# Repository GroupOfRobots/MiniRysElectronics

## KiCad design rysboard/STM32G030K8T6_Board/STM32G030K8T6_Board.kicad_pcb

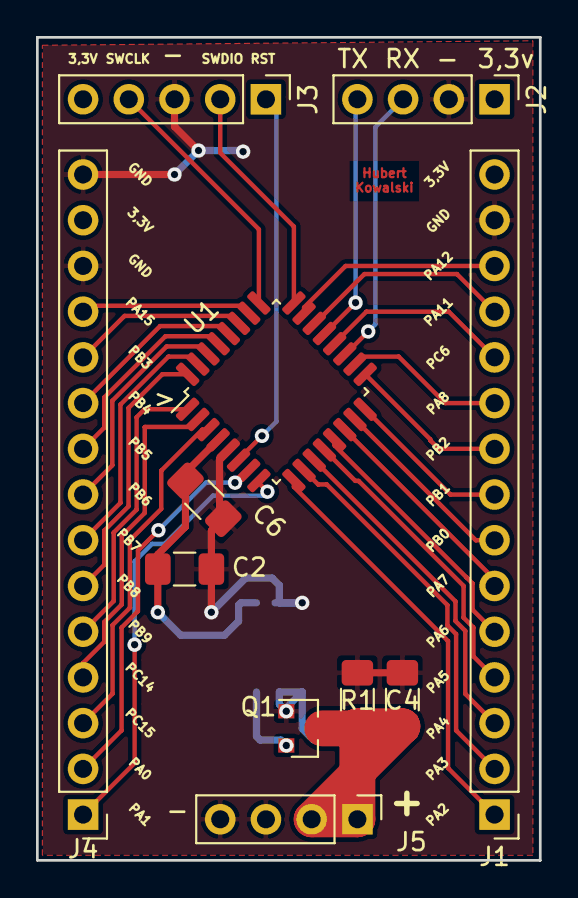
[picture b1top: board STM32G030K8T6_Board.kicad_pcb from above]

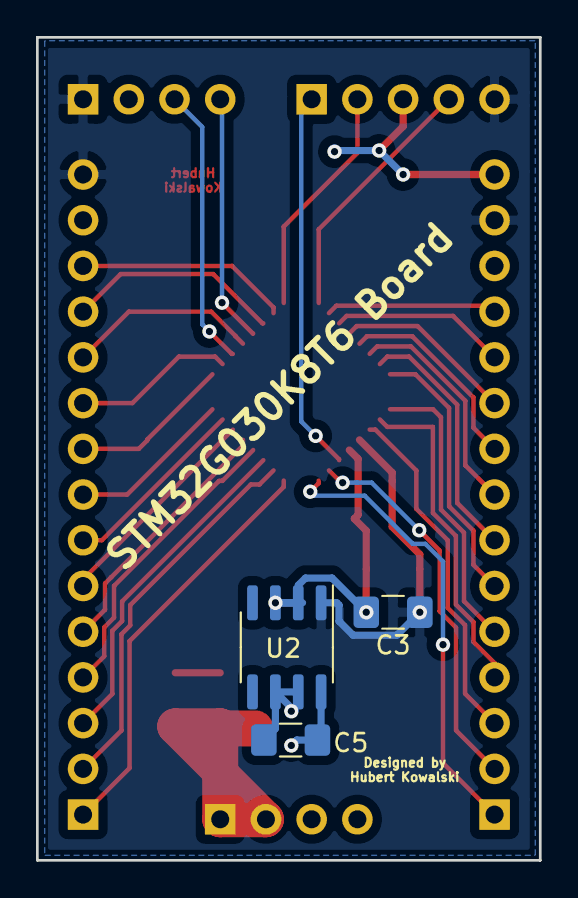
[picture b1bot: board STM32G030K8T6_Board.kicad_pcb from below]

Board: 2 copper layers, 27.9 x 45.7 mm, 14 parts (3 on the bottom side), 34 nets.

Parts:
C2, C5: 1uF; C_1206_3216Metric_Pad1.42x1.75mm_HandSolder
C3, C4, C6: 100nF; C_1206_3216Metric_Pad1.42x1.75mm_HandSolder
J1, J4: Conn_01x15; PinHeader_1x15_P2.54mm_Vertical
J2, J5: Conn_01x04; PinHeader_1x04_P2.54mm_Vertical
J3: Conn_01x05; PinHeader_1x05_P2.54mm_Vertical
Q1: IRLML6402; SOT-23
R1: 10kR; R_1206_3216Metric_Pad1.42x1.75mm_HandSolder
U1: STM32G030K8Tx; LQFP-32_7x7mm_P0.8mm
U2: L78L33_SO8; SOIC-8_3.9x4.9mm_P1.27mm

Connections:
+3V3: C2.1, C3.1, C6.1, J1.15, J2.1, J3.5, J4.14, U1.4, U2.1
/MCU_RST: J3.1, U1.6
/PA0: J4.2, U1.7
/PA1: J4.1, U1.8
/PA2: J1.1, U1.9
/PA3: J1.2, U1.10
/PA4: J1.3, U1.11
/PA5: J1.4, U1.12
/PA6: J1.5, U1.13
/PA7: J1.6, U1.14
/PA8: J1.10, U1.18
/PA9: J2.3, U1.19
/PA10: J2.4, U1.21
/PA11: J1.12, U1.22
/PA12: J1.13, U1.23
/PA15: J4.12, U1.26
/PB0: J1.7, U1.15
/PB1: J1.8, U1.16
/PB2: J1.9, U1.17
/PB3: J4.11, U1.27
/PB4: J4.10, U1.28
/PB5: J4.9, U1.29
/PB6: J4.8, U1.30
/PB7: J4.7, U1.31
/PB8: J4.6, U1.32
/PB9: J4.5, U1.1
/PC6: J1.11, U1.20
/PC14: J4.4, U1.2
/PC15: J4.3, U1.3
/SWCLK: J3.4, U1.25
/SWDIO: J3.2, U1.24
GND: C2.2, C3.2, C4.2, C5.2, C6.2, J1.14, J2.2, J3.3, J4.13, J4.15, J5.3, J5.4, Q1.1, R1.2, U1.5, U2.2, U2.3, U2.6, U2.7
unnamed: C5.1, Q1.2, U2.8
VDC: C4.1, J5.1, J5.2, Q1.3, R1.1
